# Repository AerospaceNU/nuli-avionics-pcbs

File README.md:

# Avionics PCBs

This repository contains NULI-Avionics PCB designs and reusable hardware components created with [KiCad](https://www.kicad.org/).

The repository is organized around individual PCB projects. Each PCB contains its own source files, documentation, 3D models, and fabrication outputs. Reusable components are maintained separately under `common-components/`.

**Any naming examples used below are just to show repo structure and are not indicative of good naming practices**.

## Repository Structure

```text
.
├── README.md
├── LICENSE
│
└── hardware/
    ├── boards/
    │   ├── <board-name>/
    │   │   ├── README.md
    │   │   ├── <board-name>.kicad_pro
    │   │   ├── <board-name>.kicad_sch
    │   │   ├── <board-name>.kicad_pcb
    │   │   ├── 3d-models/
    │   │   └── fabrication/
    │   │
    │   └── <another-board>/
    │       └── ...
    │
    └── common-components/
        ├── <component-name>/
        │   ├── <component-name>.kicad_sym
        │   ├── <component-name>.kicad_mod
        │   └── <component-name>.step
        │
        └── <another-component>/
            └── ...
```

## Boards

All PCB projects are located under:

```text
hardware/boards/
```

Each PCB has its own directory containing everything specific to that board.

A typical board directory has the following structure:

```text
hardware/boards/usb-c-breakout/
├── README.md
├── usb-c-breakout.kicad_pro
├── usb-c-breakout.kicad_sch
├── usb-c-breakout.kicad_pcb
├── 3d-models/
└── fabrication/
```
It will also have its own symbol and footprint library including any combination of both external and common components.
### KiCad Project Files

| File         | Description        |
| ------------ | ------------------ |
| `.kicad_pro` | KiCad project file |
| `.kicad_sch` | Schematic          |
| `.kicad_pcb` | PCB layout         |

The KiCad source files are the digital representation of the PCB design.

### 3D Models

Board-specific 3D models are stored in the board's `3d-models/` directory.

```text
3d-models/
├── enclosure.step
├── connector.step
├── mounting-bracket.step
└── <board-name>.step
```

Reusable component 3D models should also be stored with their corresponding component under `common-components/`.

### Fabrication Files

Manufacturing outputs are stored in the board's `fabrication/` directory.

Typical contents include (basically whatever the program outputs + the BOM):

```text
fabrication/
├── gerbers/
├── drill/
├── bom/
├── pick-and-place/
└── assembly/
```

Fabrication files should correspond to a specific PCB revision/release.

## Common Components

Reusable components are stored under:

```text
hardware/common-components/
```

Each component gets its own directory containing all of the resources required to use that component.

For example:

```text
hardware/common-components/
└── usb-c-receptacle/
    ├── usb-c-receptacle.kicad_sym
    ├── usb-c-receptacle.kicad_mod
    └── usb-c-receptacle.step
```

Keeping the symbol, footprint, and 3D model together makes components easy to find, copy, reuse, and version.

### Component Guidelines

A component should be placed in `common-components/` when it is intended to be reused by multiple PCB projects.

**Note that every individual PCB project should maintain its own symbols and footprints in its project files. The Common Components are meant to provide easy access to them**

Each component should use a descriptive directory name and consistent filenames:

```text
<component-name>/
├── <component-name>.kicad_sym
├── <component-name>.kicad_mod
└── <component-name>.step
```

Not every component necessarily requires all three files. For example, a component may just use a standard 0603 footprint.

## Versions and Revision History

PCB revisions are versioned independently for each board.

The repository does **not** use a single repository-wide hardware version. Each PCB project maintains its own revision history, allowing individual boards to be developed and released independently.

For example:

```text
hardware/boards/
├── usb-c-breakout/
├── power-board/
└── sensor-board/
```

Each board may have its own revision sequence:

```text
usb-c-breakout:
    v1.0.0
    v1.1.0
    v1.2.0

power-board:
    v1.0.0
    v2.0.0

sensor-board:
    v1.0.0
    v1.1.0
```

### Git History

Git commits provide the complete historical record of every PCB project.

Changes to a board should be committed with the board name and revision in the commit message.

For example:

```bash
git add hardware/boards/usb-c-breakout/
git commit -m "usb-c-breakout: Rev 1.2.0"
```

The history for an individual board can be viewed with:

```bash
git log -- hardware/boards/usb-c-breakout/
```

This shows only commits that affected that PCB.

### Board Revision Tags

When a PCB revision is considered complete, a Git tag may be created for that specific board revision.

Board tags should use the board name as a prefix:

```text
usb-c-breakout/v1.0.0
usb-c-breakout/v1.1.0
usb-c-breakout/v1.2.0

power-board/v1.0.0
power-board/v2.0.0
```

These tags are **board revision references**, not repository-wide releases.

A board revision tag identifies the exact Git commit from which that PCB revision was produced. This makes it possible to return to a known historical version of a board at any time.

### Viewing an Older Board Revision

To inspect a specific revision of a board, first identify its revision tag:

```bash
git tag --list "usb-c-breakout/*"
```

For example:

```text
usb-c-breakout/v1.0.0
usb-c-breakout/v1.1.0
usb-c-breakout/v1.2.0
```

The complete repository can be checked out at a particular board revision:

```bash
git checkout usb-c-breakout/v1.2.0
```

The `hardware/boards/usb-c-breakout/` directory will then contain the exact KiCad source files associated with that revision.

The repository does not need separate directories for historical revisions.

For example, the repository should **not** contain:

```text
usb-c-breakout-v1/
usb-c-breakout-v2/
usb-c-breakout-v3/
```

Instead, it contains one board directory whose history is maintained by Git.

### Viewing a Historical Board Without Changing the Current Checkout

A historical file can also be retrieved directly from Git:

```bash
git show usb-c-breakout/v1.2.0:hardware/boards/usb-c-breakout/usb-c-breakout.kicad_pcb
```

For more extensive work with an older revision, a separate Git worktree can be created so that the historical board can be opened in KiCad without changing the main working directory.

### Fabrication Outputs

Fabrication outputs should be associated with the board revision from which they were generated.

For example:

```text
hardware/boards/usb-c-breakout/
└── fabrication/
    ├── gerbers/
    ├── drill/
    ├── bom/
    └── assembly/
```

When a revision is finalized, the fabrication outputs should be generated from the exact source revision represented by the corresponding Git tag.

This ensures that:

```text
usb-c-breakout/v1.2.0
```

always identifies the KiCad source used to produce the Rev 1.2.0 manufacturing files.

### Revision History

Each board can maintain a revision history in its own `README.md`.

For example:

```markdown
## Revision History

| Version | Date | Changes |
|---|---|---|
| v1.0.0 | YYYY-MM-DD | Initial prototype |
| v1.1.0 | YYYY-MM-DD | Updated USB-C connector |
| v1.2.0 | YYYY-MM-DD | Changed ESD protection |
```

### Release Contents

A PCB release should include:

* KiCad schematic
* KiCad PCB layout
* KiCad project
* Board-specific 3D models
* Fabrication outputs
* BOM, when applicable
* Assembly files, when applicable
* Relevant documentation

Fabrication outputs should be generated from the same source revision represented by the release.

## PCB Documentation

Every PCB should contain its own `README.md`.

The PCB README should document:

* Authors / Contributors
* Purpose of the board
* Current revision/version
* Current development status
* Important design notes
* Manufacturing information
* Known issues
* Revision history

A PCB README can use the following template:

```markdown
# <PCB Name>

Short description of the board.

## Contributors
Authors / Contributors
## Status

**Version:** v1.0.0  
**Status:** Prototype

## Description

Describe the purpose of the board and what it is intended to do.

## Manufacturing

- Layers: ...
- Thickness: ...
- Surface finish: ...
- Minimum trace/space: ...
- Manufacturer: ...
(Basically all relavent stackup information)

## Known Issues

- Issue 1
- Issue 2

## Revision History

| Version | Date | Changes |
|---|---|---|
| v1.0.0 | YYYY-MM-DD | Initial release |

```

## Design Guidelines

### Keep Boards Self-Contained

Each board should contain **all** resources for to that board.

```text
boards/my-board/
├── README.md
├── my-board.kicad_pro
├── my-board.kicad_sch
├── my-board.kicad_pcb
├── 3d-models/
└── fabrication/
```

Avoid putting board-specific files into `common-components/`.

### Reuse Common Components

If a component is likely to be used by multiple boards, place its KiCad resources in:

```text
hardware/common-components/<component-name>/
```
Remember that this serves as a common **copy** for these resources. individual PCB directories should not depend on them, they should instead copy them into their own project files.

### Generated Files

Fabrication outputs are generated from the KiCad source files.

When possible, generated files should be associated with a specific release so that it is clear which source revision they were generated from.

## KiCad Version

The repository should document the KiCad version used to create or modify the projects when compatibility is important.

Projects should ideally be maintained using the same major KiCad version (Though its likely fine to update them, just document the new Kicad version).

## Adding a New PCB

When adding a new PCB:

1. Create a directory under `hardware/boards/`.
2. Give the directory a descriptive name.
3. Add the KiCad project, schematic, and PCB files.
4. Add a PCB-specific `README.md`.
5. Add board-specific 3D models under `3d-models/`.
6. Add fabrication outputs under `fabrication/` when appropriate.
7. Run electrical rules checks and design-rule checks.
8. Update the board documentation and revision information.

## Licensing

See `LICENSE` for information about the licensing of the hardware designs, documentation, and associated files.

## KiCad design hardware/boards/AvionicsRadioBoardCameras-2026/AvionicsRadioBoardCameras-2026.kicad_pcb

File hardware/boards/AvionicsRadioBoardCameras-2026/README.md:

# AvionicsRadioBoardCameras-2026

2026 avionics radio board: an ATSAMD21 with an E22-900MM22S LoRa module and SMA antenna connector.

## Contributors

SaiCharan Challapalli

## Status

**Version:** v1.0.0
**Status:** In development - schematic drawn, parts placed, PCB not yet routed

## Description

2026 avionics radio board: an ATSAMD21 (QFN-48) with an E22-900MM22S LoRa module and SMA antenna connector.

- KiCad project: `AvionicsRadioBoardCameras-2026.kicad_pro`, last saved with KiCad 10.0
- Schematic sheets: `AvionicsRadioBoardCameras-2026.kicad_sch` (single sheet)
- Board size: 76.8 x 50.1 mm
- `libs/`: the board's own symbols, footprints and 3D models
  - `ABS07-32.768KHZ-T/`: crystal symbol and footprints, with its STEP
  - `easyeda2kicad/`: parts imported with easyeda2kicad (E22-900MM22S symbol; footprints for the 8x8 mm inductor,
    mini-USB, SMA connector, SDA01H1SBD switch and the E22 module), with their 3D models
- `3d-models/`: board STEP export
- `fabrication/`: not generated yet (board is not routed)

## Manufacturing

- Layers: 2
- Thickness: 1.6 mm
- Surface finish: not set in the board stackup
- Minimum trace/space: 0.2 mm / 0.2 mm (default netclass)
- Manufacturer: not chosen yet

## Known Issues

From ERC/DRC run with KiCad 10.0.8 on 2026-11-05:

- PCB is not routed (169 unconnected items).
- J6: the schematic symbol's shield pin SH (GND) has no matching pad, and its two mounting PTH pads have no annular ring.
- ERC: two power symbols (#PWR032, #PWR058) are not connected, and one wire has an unconnected end.
- ERC: 16 pin-type warnings (Unspecified pins on the crystal and the E22 module connected to Passive/Bidirectional pins).
- DRC: silkscreen overlaps and silkscreen clipped by the board edge.

## Revision History

| Version | Date | Changes |
|---|---|---|
| v1.0.0 | 2026-11-05 | Added to this repo (in development, unrouted) |

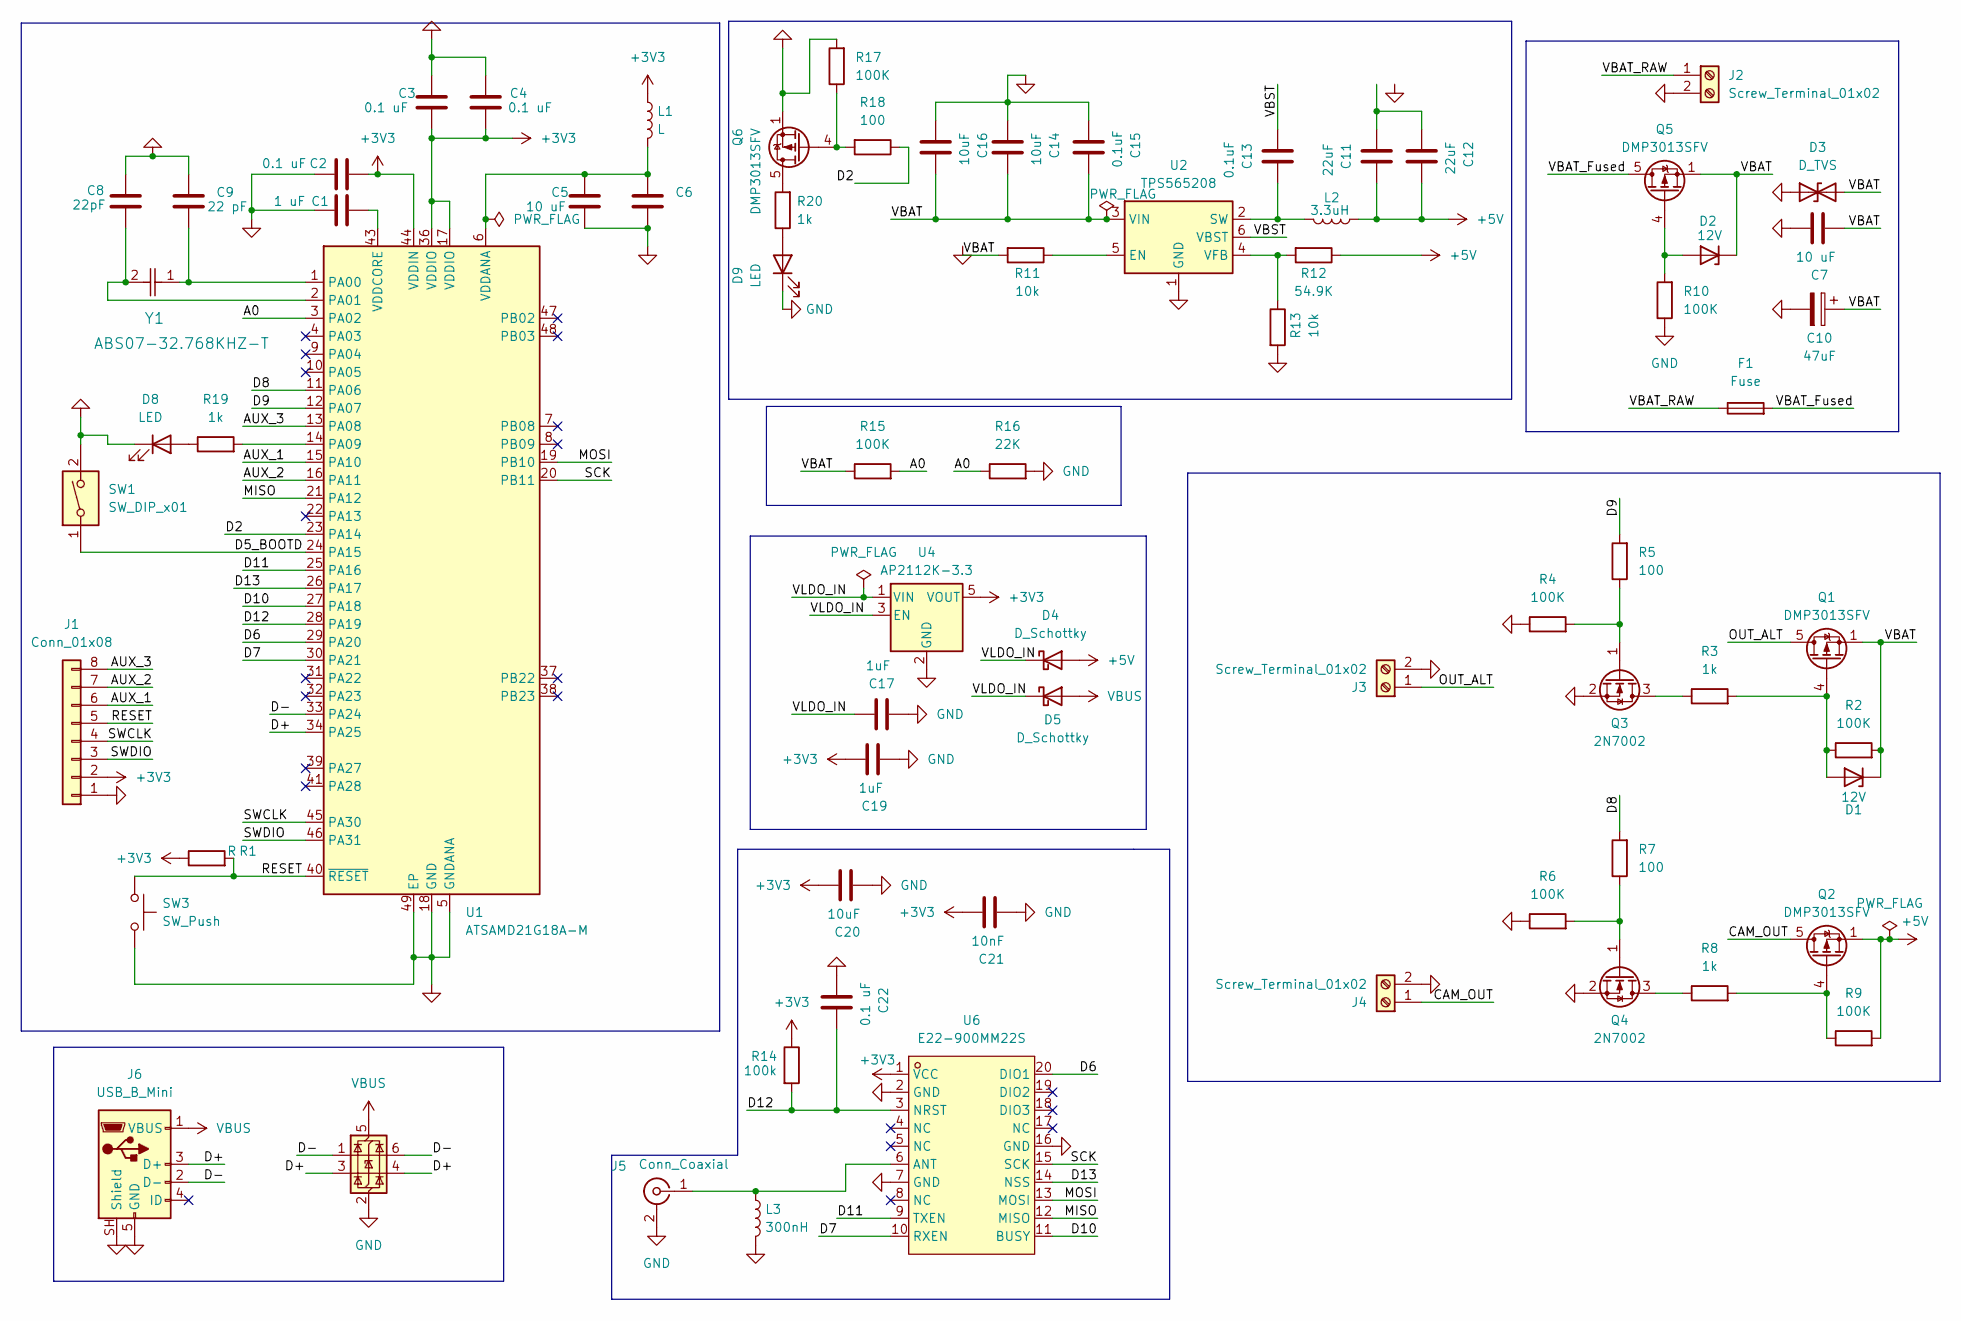
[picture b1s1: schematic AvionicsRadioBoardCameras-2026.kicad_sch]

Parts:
C1: 1 uF; C_0402_1005Metric
C2, C3, C4, C6, C22: 0.1 uF; C_0402_1005Metric
C5: 10 uF; C_0603_1608Metric
C7: 10 uF; C_1206_3216Metric
C8: 22pF; C_0402_1005Metric
C9: 22 pF; C_0402_1005Metric
C10: 47uF; CP_Elec_6.3x5.4
C11, C12: 22uF; C_1206_3216Metric
C13, C15: 0.1uF; C_0402_1005Metric
C14, C16: 10uF; C_1206_3216Metric
C17, C19: 1uF; C_0402_1005Metric
C20: 10uF; C_0805_2012Metric
C21: 10nF; C_0402_1005Metric
D1, D2: 12V; D_SOD-123
D3: D_TVS; D_SMA
D4, D5: D_Schottky; D_SOD-123
D8, D9: LED; LED_0603_1608Metric
F1: Fuse; Fuse_1206_3216Metric
J1: Conn_01x08; JST_GH_BM08B-GHS-TBT_1x08-1MP_P1.25mm_Vertical
J2, J3, J4: Screw_Terminal_01x02; TerminalBlock_Phoenix_PT-1,5-2-3.5-H_1x02_P3.50mm_Horizontal
J5: Conn_Coaxial; SMA-SMD_HJ-SMA716
J6: USB_B_Mini; MINI-USB-SMD_MINI-5PTP
L1: L; L_0603_1608Metric
L2: 3.3uH; IND-SMD_L8.0-W8.0
L3: 300nH; L_0603_1608Metric
Q1, Q2, Q5, Q6: DMP3013SFV; Diodes_PowerDI3333-8
Q3, Q4: 2N7002; SOT-23
R1: R; R_0603_1608Metric
R2, R4, R6, R9, R10, R15, R17: 100K; R_0603_1608Metric
R3, R8, R19, R20: 1k; R_0603_1608Metric
R5, R7, R18: 100; R_0603_1608Metric
R11, R13: 10k; R_0603_1608Metric
R12: 54.9K; R_0603_1608Metric
R14: 100k; R_0603_1608Metric
R16: 22K; R_0603_1608Metric
SW1: SW_DIP_x01; SW-SMD_SDA01H1SBD
SW3: SW_Push; SW_SPST_PTS810
U1: ATSAMD21G18A-M; QFN-48-1EP_7x7mm_P0.5mm_EP5.15x5.15mm
U2: TPS565208; SOT-23-6
U4: AP2112K-3.3; SOT-23-5
U5: USBLC6-2SC6; SOT-23-6
U6: E22-900MM22S; WIRELM-SMD_20P-L10.0-W10.0-P1.27-TL; MPN E22-900MM22S; LCSC Part C5333985
Y1: ABS07-32.768KHZ-T; Crystal_SMD_3215-2Pin_3.2x1.5mm

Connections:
+3V3: C2.2, C3.1, C4.1, C19.1, C20.1, C21.1, J1.2, L1.1, R1.1, R14.1, U1.17 (VDDIO), U1.36 (VDDIO), U1.44 (VDDIN), U4.5 (VOUT), U6.1 (VCC)
+5V: C11.1, C12.1, D4.2 (A), L2.1, Q2.1 (S), Q2.2 (S), Q2.3 (S), R9.2, R12.1
/A0: R15.2, R16.1, U1.3 (PA02)
/AUX_1: J1.6, U1.15 (PA10)
/AUX_2: J1.7, U1.16 (PA11)
/AUX_3: J1.8, U1.13 (PA08)
/CAM_OUT: J4.1, Q2.5 (D)
/D2: R18.1, U1.23 (PA14)
/D5_BOOTD: SW1.1, U1.24 (PA15)
/D6: U1.29 (PA20), U6.20 (DIO1)
/D7: U1.30 (PA21), U6.10 (RXEN)
/D8: R7.2, U1.11 (PA06)
/D9: R5.2, U1.12 (PA07)
/D10: U1.27 (PA18), U6.11 (BUSY)
/D11: U1.25 (PA16), U6.9 (TXEN)
/D12: C22.1, R14.2, U1.28 (PA19), U6.3 (NRST)
/D13: U1.26 (PA17), U6.14 (NSS)
/D+: J6.3 (D+), U1.34 (PA25), U5.3 (I/O2), U5.4 (I/O2)
/D-: J6.2 (D-), U1.33 (PA24), U5.1 (I/O1), U5.6 (I/O1)
/MISO: U1.21 (PA12), U6.12 (MISO)
/MOSI: U1.19 (PB10), U6.13 (MOSI)
/OUT_ALT: J3.1, Q1.5 (D)
/RESET: J1.5, R1.2, SW3.1, U1.40 (~RESET)
/SCK: U1.20 (PB11), U6.15 (SCK)
/SWCLK: J1.4, U1.45 (PA30)
/SWDIO: J1.3, U1.46 (PA31)
/VBAT: C7.2, C10.1, C14.1, C15.1, C16.1, D1.1 (K), D2.1 (K), D3.2 (A2), Q1.1 (S), Q1.2 (S), Q1.3 (S), Q5.1 (S), Q5.2 (S), Q5.3 (S), R2.2, R11.2, R15.1, U2.3 (VIN)
/VBAT_Fused: F1.2, Q5.5 (D)
/VBAT_RAW: F1.1, J2.1
/VBST: C13.2, U2.6 (VBST)
/VLDO_IN: C17.1, D4.1 (K), D5.1 (K), U4.1 (VIN), U4.3 (EN)
GND: C1.2, C2.1, C3.2, C4.2, C5.1, C6.1, C7.1, C8.1, C9.1, C10.2, C14.2, C15.2, C16.2, C17.2, C19.2, C20.2, C21.2, C22.2, D3.1 (A1), D8.1 (K), D9.1 (K), J1.1, J2.2, J3.2, J4.2, J5.2 (Ext), J6.5 (GND), J6.SH (Shield), L3.2, Q3.2 (S), Q4.2 (S), Q6.1 (S), Q6.2 (S), Q6.3 (S), R4.1, R6.1, R10.1, R13.2, R16.2, R17.2, SW1.2, SW3.2, U1.5 (GNDANA), U1.18 (GND), U1.35 (GND), U1.42 (GND), U1.49 (EP), U2.1 (GND), U4.2 (GND), U5.2 (GND), U6.2 (GND), U6.7 (GND), U6.16 (GND)
unnamed: C11.2, C12.2
unnamed: D1.2 (A), Q1.4 (G), R2.1, R3.2
unnamed: D2.2 (A), Q5.4 (G), R10.2
unnamed: D8.2 (A), R19.1
unnamed: D9.2 (A), R20.1
unnamed: J5.1 (In), L3.1, U6.6 (ANT)
unnamed: Q2.4 (G), R8.2, R9.1
unnamed: Q3.3 (D), R3.1
unnamed: Q3.1 (G), R4.2, R5.1
unnamed: Q4.3 (D), R8.1
unnamed: Q4.1 (G), R6.2, R7.1
unnamed: Q6.5 (D), R20.2
unnamed: Q6.4 (G), R17.1, R18.2
unnamed: C9.2, U1.1 (PA00), Y1.1
unnamed: C8.2, U1.2 (PA01), Y1.2
unnamed: R19.2, U1.14 (PA09)
unnamed: C5.2, C6.2, L1.2, U1.6 (VDDANA)
unnamed: C1.1, U1.43 (VDDCORE)
unnamed: R11.1, U2.5 (EN)
unnamed: C13.1, L2.2, U2.2 (SW)
unnamed: R12.2, R13.1, U2.4 (VFB)
VBUS: D5.2 (A), J6.1 (VBUS), U5.5 (VBUS)

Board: 2 copper layers, 72 parts (0 on the bottom side), 54 nets, no tracks yet.

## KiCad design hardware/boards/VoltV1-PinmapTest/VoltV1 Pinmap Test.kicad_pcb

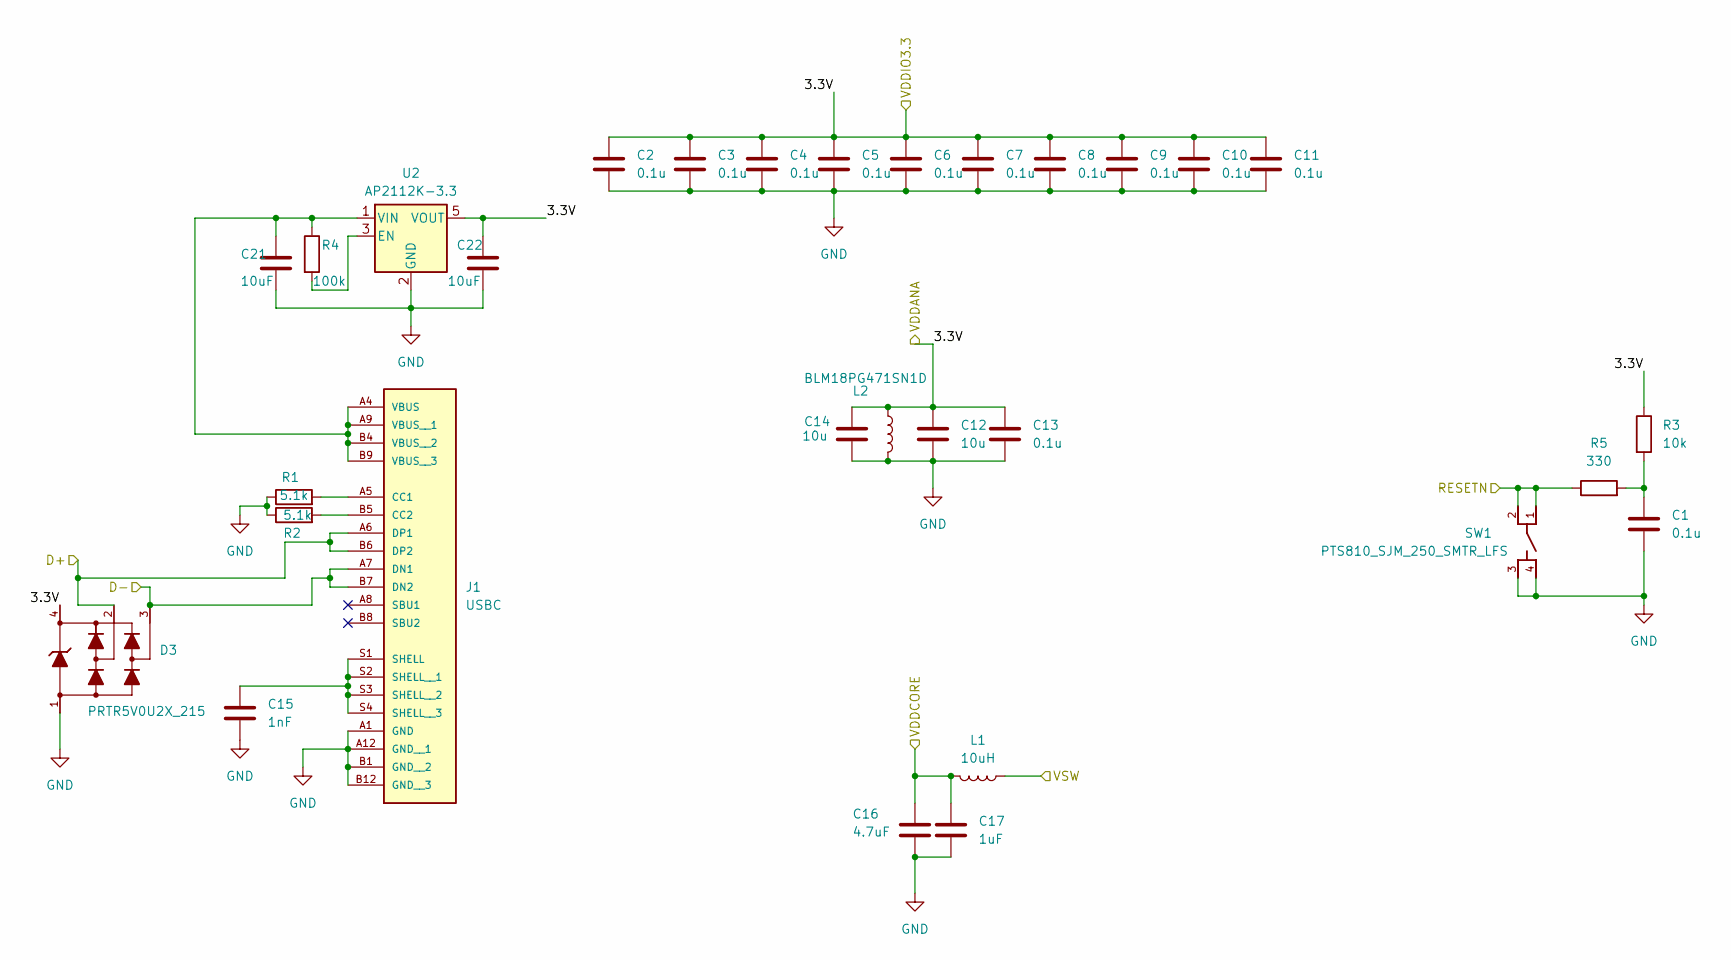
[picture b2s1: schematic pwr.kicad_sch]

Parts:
C1, C2, C3, C4, C5, C6, C7, C8, C9, C10, C11, C13: 0.1u; C_0603_1608Metric
C12, C14: 10u; C_0603_1608Metric
C15: 1nF; C_0603_1608Metric
C16: 4.7uF; C_0603_1608Metric
C17: 1uF; C_0603_1608Metric
C21, C22: 10uF; C_0603_1608Metric
D3: PRTR5V0U2X_215; SOT143B
J1: USBC; PARTREV B
L1: 10uH; L_0603_1608Metric
L2: BLM18PG471SN1D; L_0603_1608Metric
R1, R2: 5.1k; R_0603_1608Metric
R3: 10k; R_0603_1608Metric
R4: 100k; R_0603_1608Metric
R5: 330; R_0603_1608Metric
SW1: PTS810_SJM_250_SMTR_LFS; SW_PTS810_SJM_250_SMTR_LFS
U2: AP2112K-3.3; SOT-23-5

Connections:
/mcu/D+: D3.2, J1.A6 (DP1), J1.B6 (DP2); also elsewhere on the board
/mcu/D-: D3.3, J1.A7 (DN1), J1.B7 (DN2); also elsewhere on the board
/mcu/RESETN: R5.1, SW1.1, SW1.2; also elsewhere on the board
/mcu/VDDCORE: C16.1, C17.1, L1.2; also elsewhere on the board
/mcu/VSW: L1.1; also elsewhere on the board
/pwr/3.3V: C2.1, C3.1, C4.1, C5.1, C6.1, C7.1, C8.1, C9.1, C10.1, C11.1, C12.1, C13.1, C14.1, C22.1, D3.4, L2.1, R3.1, U2.5 (VOUT); also elsewhere on the board
GND: C1.2, C2.2, C3.2, C4.2, C5.2, C6.2, C7.2, C8.2, C9.2, C10.2, C11.2, C12.2, C13.2, C14.2, C15.2, C16.2, C17.2, C21.2, C22.2, D3.1, J1.A1 (GND), J1.A12 (GND__1), J1.B1 (GND__2), J1.B12 (GND__3), L2.2, R1.1, R2.1, SW1.3, SW1.4, U2.2 (GND); also elsewhere on the board
unnamed: C1.1, R3.2, R5.2
unnamed: J1.A5 (CC1), R1.2
unnamed: J1.B5 (CC2), R2.2
unnamed: C15.1, J1.S1 (SHELL), J1.S2 (SHELL__1), J1.S3 (SHELL__2), J1.S4 (SHELL__3)
unnamed: C21.1, J1.A4 (VBUS), J1.A9 (VBUS__1), J1.B4 (VBUS__2), J1.B9 (VBUS__3), R4.1, U2.1 (VIN)
unnamed: R4.2, U2.3 (EN)

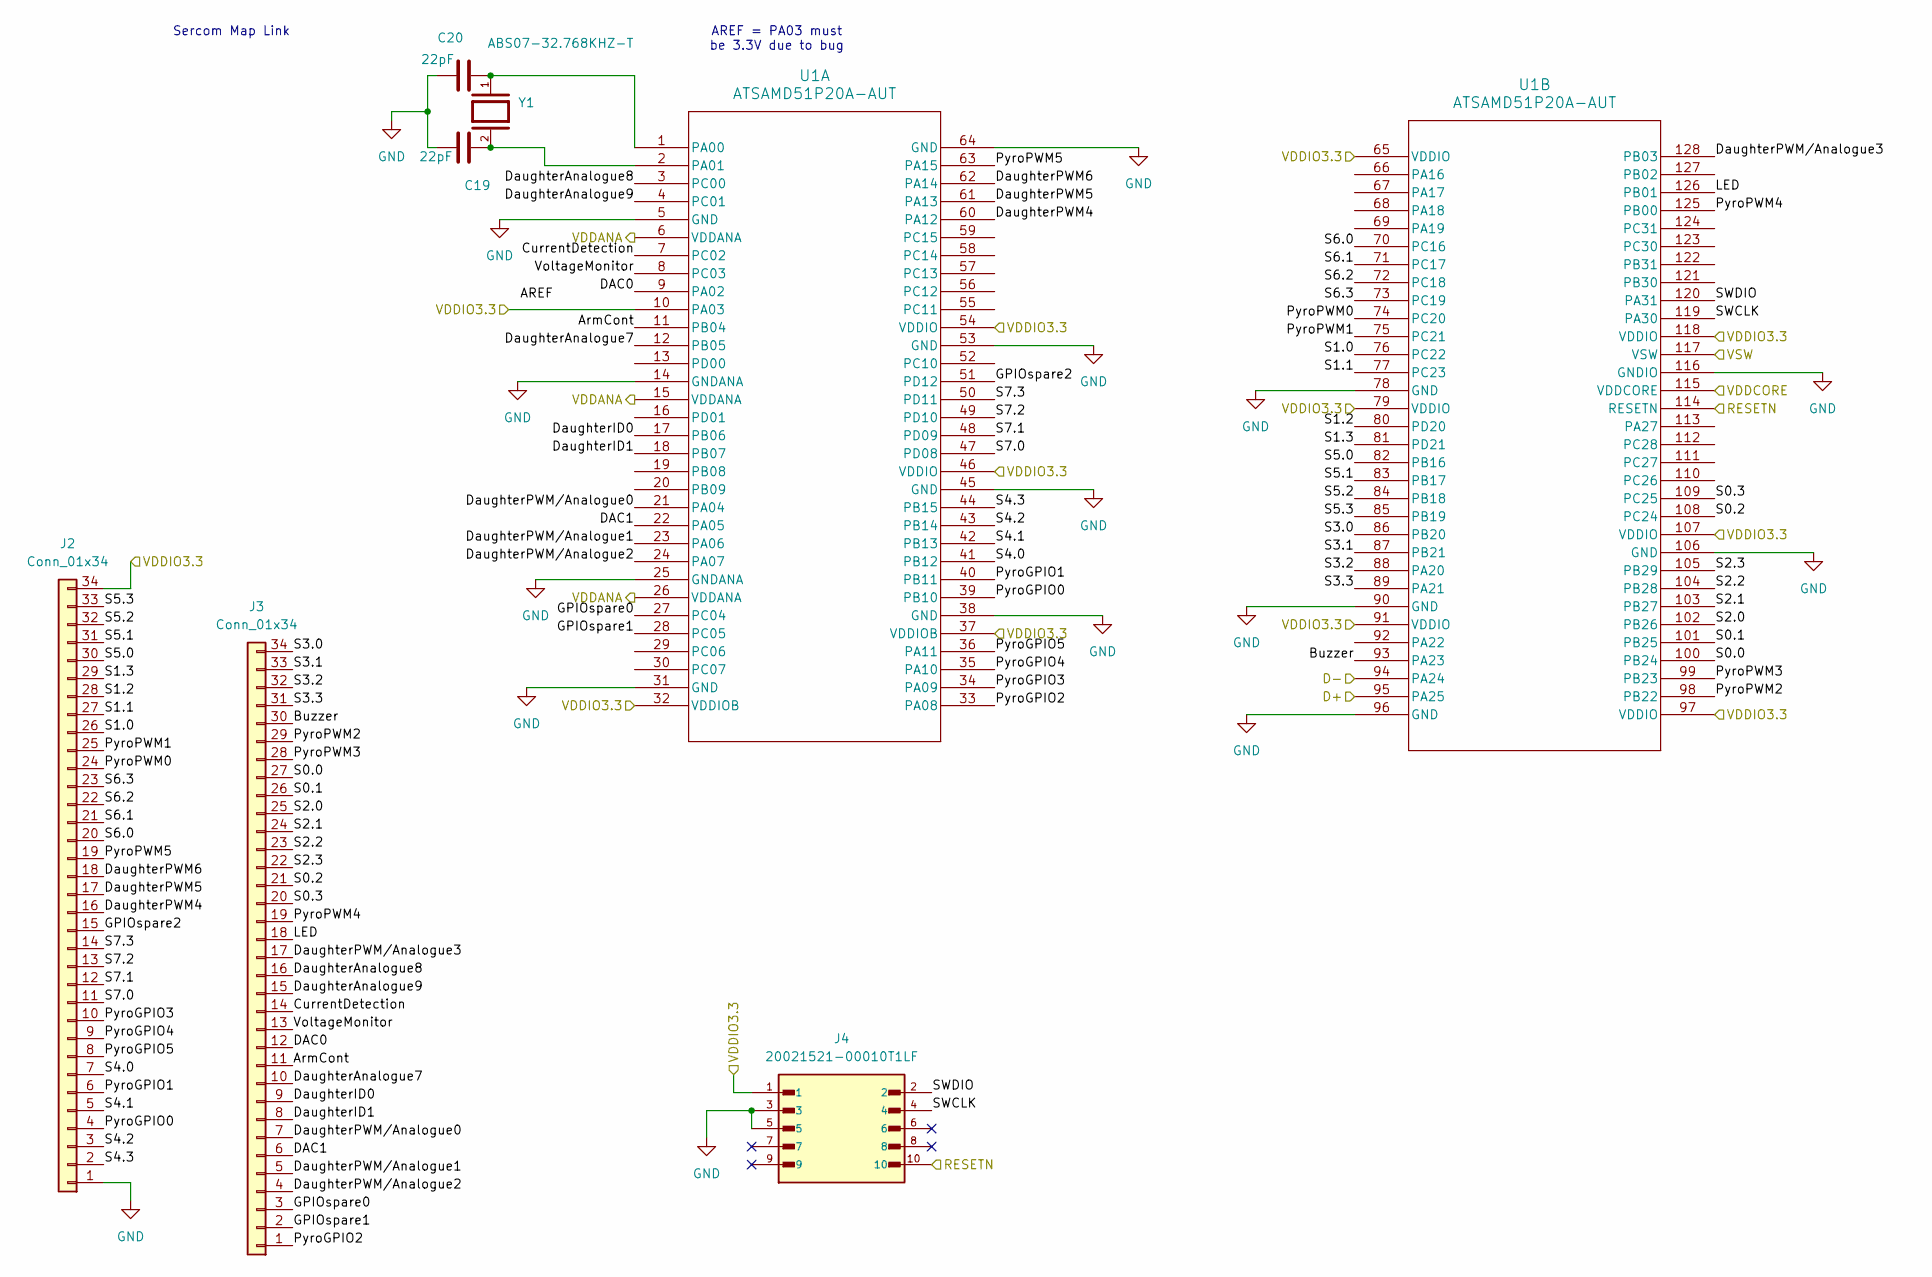
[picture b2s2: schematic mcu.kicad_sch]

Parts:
C19, C20: 22pF; C_0603_1608Metric
J2, J3: Conn_01x34; PinHeader_1x34_P2.54mm_Vertical
J4: 20021521-00010T1LF; AMPHENOL_20021521-00010T1LF; PARTREV N
U1: ATSAMD51P20A-AUT
Y1: ABS07-32.768KHZ-T; XTAL_ABS07-32.768KHZ-T; PARTREV 08.19.15

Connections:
/mcu/ArmCont: J3.11, U1.11 (PB04)
/mcu/Buzzer: J3.30, U1.93 (PA23)
/mcu/CurrentDetection: J3.14, U1.7 (PC02)
/mcu/D+: U1.95 (PA25); also elsewhere on the board
/mcu/D-: U1.94 (PA24); also elsewhere on the board
/mcu/DAC0: J3.12, U1.9 (PA02)
/mcu/DAC1: J3.6, U1.22 (PA05)
/mcu/DaughterAnalogue7: J3.10, U1.12 (PB05)
/mcu/DaughterAnalogue8: J3.16, U1.3 (PC00)
/mcu/DaughterAnalogue9: J3.15, U1.4 (PC01)
/mcu/DaughterID0: J3.9, U1.17 (PB06)
/mcu/DaughterID1: J3.8, U1.18 (PB07)
/mcu/DaughterPWM4: J2.16, U1.60 (PA12)
/mcu/DaughterPWM5: J2.17, U1.61 (PA13)
/mcu/DaughterPWM6: J2.18, U1.62 (PA14)
/mcu/DaughterPWM/Analogue0: J3.7, U1.21 (PA04)
/mcu/DaughterPWM/Analogue1: J3.5, U1.23 (PA06)
/mcu/DaughterPWM/Analogue2: J3.4, U1.24 (PA07)
/mcu/DaughterPWM/Analogue3: J3.17, U1.128 (PB03)
/mcu/GPIOspare0: J3.3, U1.27 (PC04)
/mcu/GPIOspare1: J3.2, U1.28 (PC05)
/mcu/GPIOspare2: J2.15, U1.51 (PD12)
/mcu/LED: J3.18, U1.126 (PB01)
/mcu/PyroGPIO0: J2.4, U1.39 (PB10)
/mcu/PyroGPIO1: J2.6, U1.40 (PB11)
/mcu/PyroGPIO2: J3.1, U1.33 (PA08)
/mcu/PyroGPIO3: J2.10, U1.34 (PA09)
/mcu/PyroGPIO4: J2.9, U1.35 (PA10)
/mcu/PyroGPIO5: J2.8, U1.36 (PA11)
/mcu/PyroPWM0: J2.24, U1.74 (PC20)
/mcu/PyroPWM1: J2.25, U1.75 (PC21)
/mcu/PyroPWM2: J3.29, U1.98 (PB22)
/mcu/PyroPWM3: J3.28, U1.99 (PB23)
/mcu/PyroPWM4: J3.19, U1.125 (PB00)
/mcu/PyroPWM5: J2.19, U1.63 (PA15)
/mcu/RESETN: J4.10, U1.114 (RESETN); also elsewhere on the board
/mcu/S0.0: J3.27, U1.100 (PB24)
/mcu/S0.1: J3.26, U1.101 (PB25)
/mcu/S0.2: J3.21, U1.108 (PC24)
/mcu/S0.3: J3.20, U1.109 (PC25)
/mcu/S1.0: J2.26, U1.76 (PC22)
/mcu/S1.1: J2.27, U1.77 (PC23)
/mcu/S1.2: J2.28, U1.80 (PD20)
/mcu/S1.3: J2.29, U1.81 (PD21)
/mcu/S2.0: J3.25, U1.102 (PB26)
/mcu/S2.1: J3.24, U1.103 (PB27)
/mcu/S2.2: J3.23, U1.104 (PB28)
/mcu/S2.3: J3.22, U1.105 (PB29)
/mcu/S3.0: J3.34, U1.86 (PB20)
/mcu/S3.1: J3.33, U1.87 (PB21)
/mcu/S3.2: J3.32, U1.88 (PA20)
/mcu/S3.3: J3.31, U1.89 (PA21)
/mcu/S4.0: J2.7, U1.41 (PB12)
/mcu/S4.1: J2.5, U1.42 (PB13)
/mcu/S4.2: J2.3, U1.43 (PB14)
/mcu/S4.3: J2.2, U1.44 (PB15)
/mcu/S5.0: J2.30, U1.82 (PB16)
/mcu/S5.1: J2.31, U1.83 (PB17)
/mcu/S5.2: J2.32, U1.84 (PB18)
/mcu/S5.3: J2.33, U1.85 (PB19)
/mcu/S6.0: J2.20, U1.70 (PC16)
/mcu/S6.1: J2.21, U1.71 (PC17)
/mcu/S6.2: J2.22, U1.72 (PC18)
/mcu/S6.3: J2.23, U1.73 (PC19)
/mcu/S7.0: J2.11, U1.47 (PD08)
/mcu/S7.1: J2.12, U1.48 (PD09)
/mcu/S7.2: J2.13, U1.49 (PD10)
/mcu/S7.3: J2.14, U1.50 (PD11)
/mcu/SWCLK: J4.4, U1.119 (PA30)
/mcu/SWDIO: J4.2, U1.120 (PA31)
/mcu/VDDCORE: U1.115 (VDDCORE); also elsewhere on the board
/mcu/VSW: U1.117 (VSW); also elsewhere on the board
/mcu/VoltageMonitor: J3.13, U1.8 (PC03)
/pwr/3.3V: J2.34, J4.1, U1.6 (VDDANA), U1.10 (PA03), U1.15 (VDDANA), U1.26 (VDDANA), U1.32 (VDDIOB), U1.37 (VDDIOB), U1.46 (VDDIO), U1.54 (VDDIO), U1.65 (VDDIO), U1.79 (VDDIO), U1.91 (VDDIO), U1.97 (VDDIO), U1.107 (VDDIO), U1.118 (VDDIO); also elsewhere on the board
GND: C19.2, C20.2, J2.1, J4.3, J4.5, U1.5 (GND), U1.14 (GNDANA), U1.25 (GNDANA), U1.31 (GND), U1.38 (GND), U1.45 (GND), U1.53 (GND), U1.64 (GND), U1.78 (GND), U1.90 (GND), U1.96 (GND), U1.106 (GND), U1.116 (GNDIO); also elsewhere on the board
unnamed: C20.1, U1.1 (PA00), Y1.1
unnamed: C19.1, U1.2 (PA01), Y1.2

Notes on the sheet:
Sercom Map Link
AREF = PA03 must be 3.3V due to bug

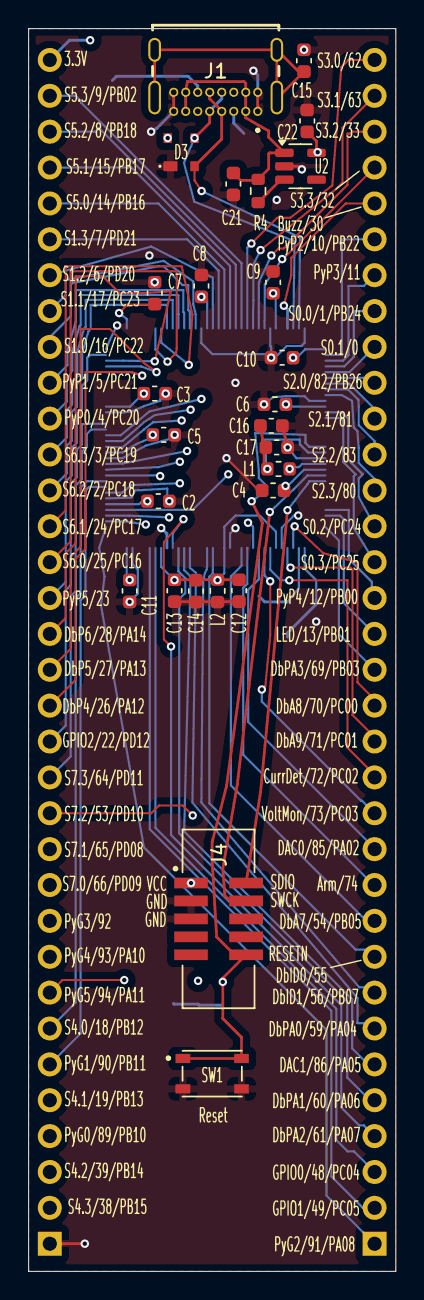
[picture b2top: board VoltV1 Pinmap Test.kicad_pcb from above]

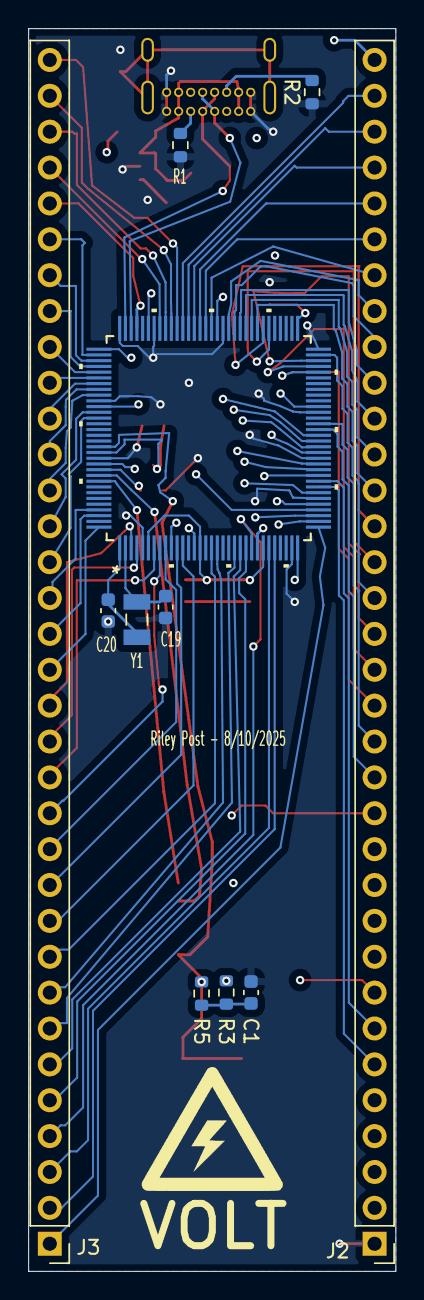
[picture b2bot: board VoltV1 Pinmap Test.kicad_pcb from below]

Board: 4 copper layers, 26.0 x 88.0 mm, 37 parts (11 on the bottom side), 83 nets.

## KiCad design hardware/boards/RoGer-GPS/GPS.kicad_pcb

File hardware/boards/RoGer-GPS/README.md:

# RoGer-GPS

RoGer GPS board.

## Contributors

irelandhunter

## Status

**Version:** not recorded (the board's title block has no revision)
**Status:** Moved here from CADLab NULIAvionics/RoGer; this folder is now the working copy.

## Description

RoGer GPS board.

- KiCad project: `GPS.kicad_pro`, last saved with KiCad 9.0
- Schematic sheets: `GPS.kicad_sch`
- Board size: 61.0 x 39.5 mm
- No fabrication outputs were in the source repo.

## Manufacturing

- Layers: 4
- Thickness: 1.6 mm
- Surface finish: not set in the board stackup
- Minimum trace/space: 0.157 mm / 0.2 mm (smallest track on the board / default netclass clearance)
- Minimum drill: 0.25 mm (design rule)
- Manufacturer: not recorded

## Known Issues

- Its library tables point at another machine's folders, so KiCad warns about missing libraries; the symbols and footprints stored in the design still open fine, and the parts are in `hardware/common-components/`.

## Revision History

| Version | Date | Changes |
|---|---|---|
| - | 2026-02-07 | Moved into this repo from CADLab NULIAvionics/RoGer (history from 2026-02-07 to 2026-02-07 stays there) |

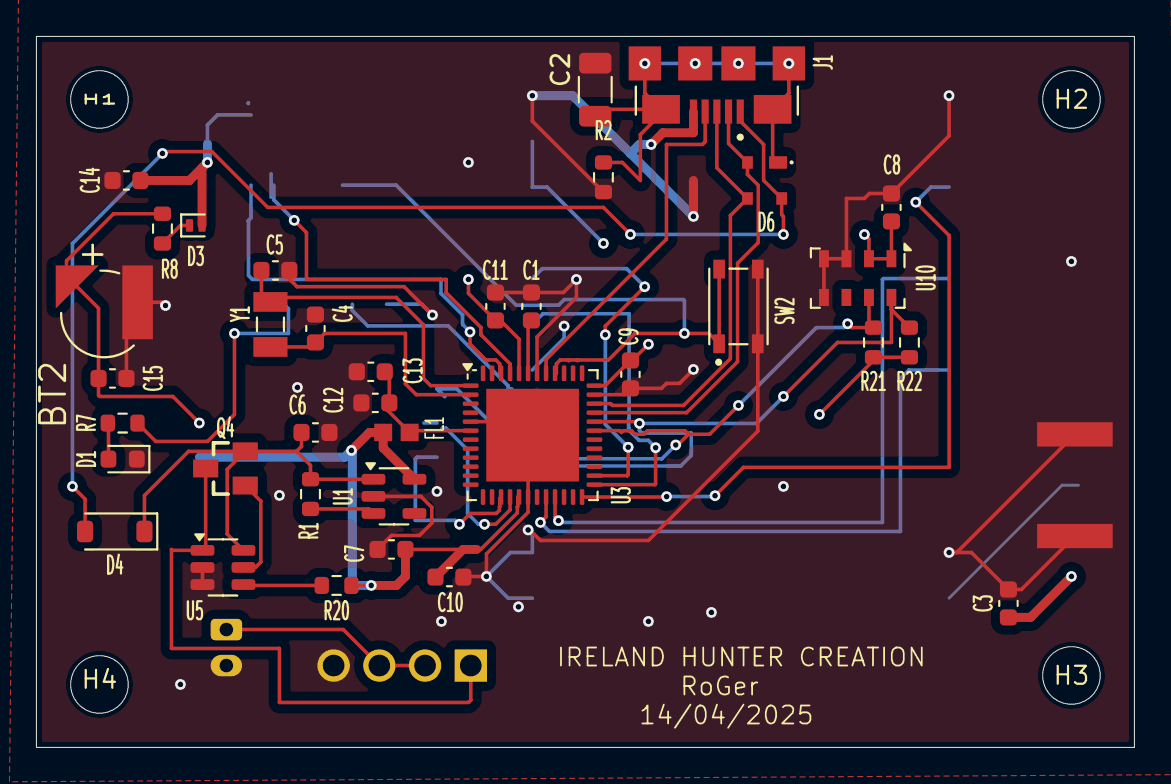
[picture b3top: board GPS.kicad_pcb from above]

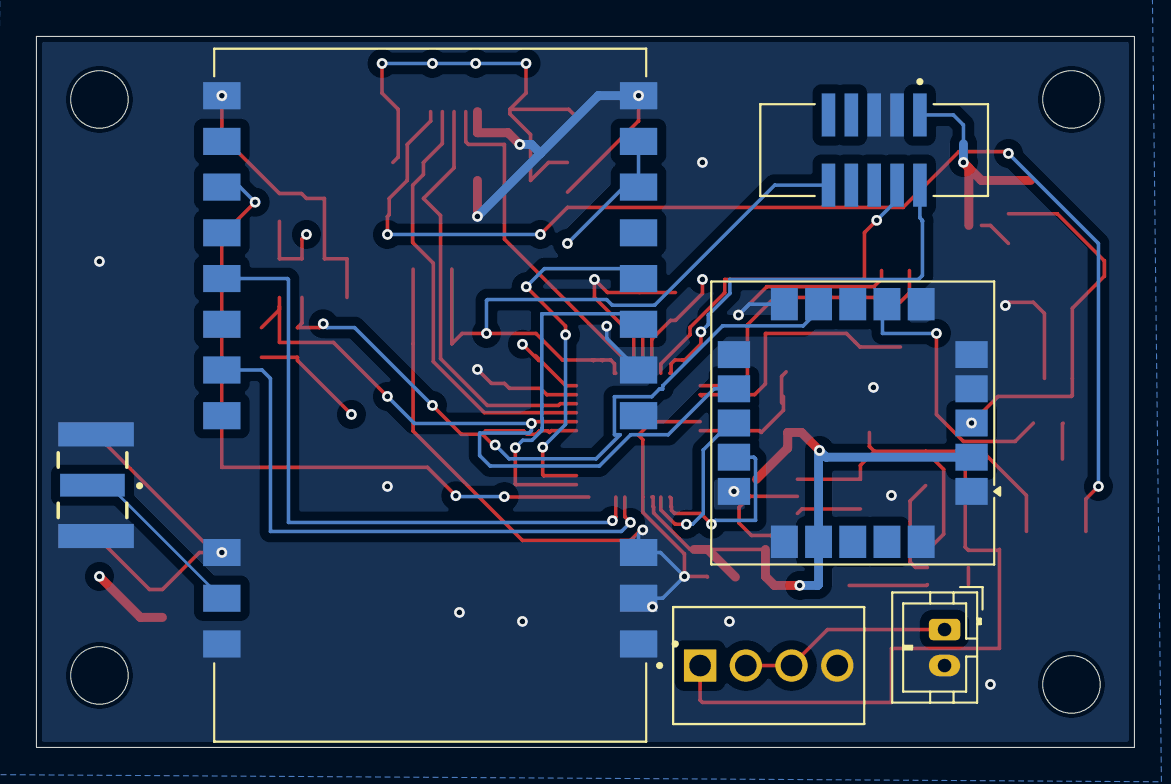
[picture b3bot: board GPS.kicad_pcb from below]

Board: 4 copper layers, 61.0 x 39.5 mm, 46 parts (6 on the bottom side), 34 nets.

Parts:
BT2: ML414H_IV01E; SEIKO_ML414H_IV01E
C1, C14, C15: 1uF; C_0603_1608Metric
C2: 4.7nF; C_1206_3216Metric
C3, C6, C7: 10uF; C_0603_1608Metric
C4, C5: 22pF; C_0603_1608Metric
C8, C9, C10, C11, C13: 0.1uF; C_0603_1608Metric
C12: 4.7uF; C_0603_1608Metric
D1: LED; LED_0603_1608Metric
D3: D_Schottky; D_SOD-882
D4: D_Schottky; D_SOD-123
D6: PRTR5V0U2X_215; SOT143B
FL1: BLM18PG471SN1D; BEADC1608X95N
H1, H2, H3, H4: MountingHole; MountingHole_3.2mm_M3
J1: ZX62-AB-5PA_31_; HIROSE_ZX62-AB-5PA_31_
J3: SMA-J-P-H-ST-EM1; SAMTEC_SMA-J-P-H-ST-EM1
J4: Conn_01x04; TE_282834-4
J5: Conn_01x02; JST_PH_B2B-PH-K_1x02_P2.00mm_Vertical
J6: 20021521-00010T1LF; AMPHENOL_20021521-00010T1LF
Q4: FDN306P; SSOT-3
R1: 100k; R_0603_1608Metric
R2, R20: 1M; R_0603_1608Metric
R7: 2k; R_0603_1608Metric
R8: 3.3k; R_0603_1608Metric
R21, R22: 2.2k; R_0603_1608Metric
SW2: PTS810_SJM_250_SMTR_LFS; SW_PTS810_SJM_250_SMTR_LFS
U1: AP2112K-3.3; SOT-23-5
U2: SAM-M8Q; ublox_SAM-M8Q
U3: ATSAMD21G18A-M; QFN-48-1EP_7x7mm_P0.5mm_EP5.15x5.15mm
U5: LTC4412xS6; TSOT-23-6
U6: E22-900M30S; XCVR_E22-900M30S
U10: MS5607-02BA; LGA-8_3x5mm_P1.25mm
Y1: ABS07-32.768KHZ-T; XTAL_ABS07-32.768KHZ-T

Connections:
+3.3V: C3.1, C7.1, C8.1, C9.1, C10.1, C11.2, C14.2, D3.2 (A), FL1.2, J6.1, R20.2, R21.2, R22.2, U1.5 (VOUT), U2.2 (VCC_IO), U2.17 (VCC), U3.17 (VDDIO), U3.36 (VDDIO), U3.44 (VDDIN), U6.9 (VCC), U6.10 (VCC), U10.1 (VDD), U10.2 (PS)
/STATUS: R20.1, U5.4 (STAT)
/TIMEPULSE: D1.2 (A), R7.1
/VBAT: J4.1, Q4.3, U5.1 (VIN)
BUSY: U3.24 (PA15), U6.14 (BUSY)
D+: D6.3, J1.3 (D+), U3.34 (PA25)
D-: D6.2, J1.2 (D-), U3.33 (PA24)
GND: BT2.2, C1.1, C2.2, C3.2, C4.1, C5.1, C6.2, C7.2, C8.2, C9.2, C10.2, C11.1, C12.2, C13.2, C14.1, C15.2, D1.1 (K), J1.5 (GND), J3.2_1, J3.2_2, J3.3_1, J3.3_2, J4.4, J5.2, J6.3, J6.5, R2.2, SW2.3, SW2.4, U1.2 (GND), U2.1 (GND), U2.4 (GND), U2.5 (GND), U2.6 (GND), U2.10 (GND), U2.11 (GND), U2.15 (GND), U2.16 (GND), U2.20 (GND), U3.5 (GNDANA), U3.18 (GND), U3.35 (GND), U3.42 (GND), U3.49 (EP), U5.2 (GND), U5.3 (CTL), U6.1 (GND), U6.2 (GND), U6.3 (GND), U6.4 (GND), U6.5 (GND), U6.11 (GND), U6.12 (GND), U6.20 (GND), U6.22 (GND), U10.3 (GND), U10.4 (CSB), U10.5 (CSB)
HOST: J1.4 (ID), U3.41 (PA28)
MIS0: U3.21 (PA12), U6.16 (MISO)
unnamed: D3.1 (K), R8.1
unnamed: C6.1, D4.1 (K), Q4.2, R1.1, U1.1 (VIN), U5.6 (SENSE)
unnamed: J4.2, J4.3, J5.1
unnamed: R1.2, U1.3 (EN)
unnamed: R7.2, U2.7 (TIMEPULSE)
unnamed: BT2.1, C15.1, R8.2, U2.3 (V_BCKP)
unnamed: C5.2, U3.1 (PA00), Y1.2
unnamed: C4.2, U3.2 (PA01), Y1.1
unnamed: C12.1, C13.1, FL1.1, U3.6 (VDDANA)
unnamed: C1.2, U3.43 (VDDCORE)
unnamed: Q4.1, U5.5 (GATE)
unnamed: J3.1, U6.21 (ANT)
RESET: J6.10, SW2.1, SW2.2, U3.40 (~RESET)
RX: U2.13 (TXD), U3.16 (PA11)
RXEN: U3.25 (PA16), U6.6 (RXEN)
SCK: U3.20 (PB11), U6.18 (SCK)
SCL: R22.1, U2.12 (SCL), U3.32 (PA23), U10.8 (SCLK)
SDA: R21.1, U2.9 (SDA), U3.31 (PA22), U10.7 (SDI/SDA)
SHIELD: C2.1, D6.1, J1.S1 (SHIELD), J1.S2 (SHIELD), J1.S3 (SHIELD), J1.S4 (SHIELD), J1.S5 (SHIELD), J1.S6 (SHIELD), R2.1
SWCLK: J6.4, U3.45 (PA30)
SWDI0: J6.2, U3.46 (PA31)
TX: U2.14 (RXD), U3.15 (PA10)
TXEN: U3.26 (PA17), U6.7 (TXEN)
VUSB: D4.2 (A), D6.4, J1.1 (VCC)
